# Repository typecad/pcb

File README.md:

# [typeCAD/pcb](https://github.com/typeCAD/pcb)

🤖 programmatically 💥 create 🛰️ hardware

**typeCAD** is a way to programmatically create hardware designs — KiCAD + TypeScript + npm. `@typecad/pcb` is the core package: schematics, PCB layout, placement, autorouting, zones, stitching, simulation, and a built-in gerber board viewer, with passives built in.

It's done with TypeScript and all the awesomeness of the npm/Node.js ecosystem.

- npm packages can be imported into your projects
- create portable/importable/shareable packages
- semantic version control

The schematic portion of hardware design is replaced with a few simple TypeScript classes. Rather than clicking and dragging, a line of code creates a component, and another line connects it. Sections of code can be turned into reusable modules and those modules can be turned into npm packages.

Code can be version controlled, status tracked, git push/pull/PR/issues can be used, and all the typical tools for software design can be used for hardware design now

## Example
_This **type**CAD code..._
```ts
import { Component, PCB, Resistor, LED } from '@typecad/pcb'

let typecad = new PCB('typecad');
let bt1 = new Component({ footprint: 'Battery:BatteryHolder_Keystone_500' });
let r1 = new Resistor({ value: '1 kOhm', size: '0805' });
let d1 = new LED();

typecad.named('vin').net(bt1.pin(1), r1.pin(1));
typecad.net(r1.pin(2), d1.pin(2));
typecad.named('gnd').net(d1.pin(1), bt1.pin(2));

typecad.create(r1, d1, bt1);
```

_...is the same as this schematic._

>The difference is that code can be copied, turned into reusable packages, version controlled, and used within the npm/Node.js system.

## Passives

Resistors, capacitors, inductors, diodes, LEDs, and fuses are built in — no second package. The SMD package size is a constructor option (default `0603`), and an explicit `footprint` always wins:

```ts
import { PCB, Resistor, Capacitor, Connector, TestPoint, MountingHole, NetTie } from '@typecad/pcb'

let r1 = new Resistor({ value: '4.7 kOhm' });                 // 0603 (default)
let r2 = new Resistor({ value: '10 kOhm', size: '0805' });    // explicit size
let c1 = new Capacitor({ value: '100 nF', voltage: '6.3 V' });
let j1 = new Connector({ number: 4, series: 'JST-SH' });      // footprint templated from the pin count
```

Sizes: `'0201' | '0402' | '0603' | '0805' | '1206' | '1210'` (fuses from `'0603'` up). Inside a `Package`, `this.passives.Capacitor(...)` works out of the box; shift a whole package with `{ passiveSize: '0805' }`.

## Get started
Read through the [documentation](https://typecad.net/getting-started) for a full walkthrough:

```bash
npx @typecad/pcb create
```

## Board viewer

This package ships a built-in, zero-dependency Gerber (RS-274X) + Excellon viewer:

```bash
# one-shot: render a fab-output directory to a self-contained interactive HTML file
npx gerber-viewer gerbers/ -o board-view.html --open
```

A ruler button in the toolbar arms a measurement mode: click a start point, move the mouse to
see the live distance, click again to stick the ruler — measurements accumulate, and `Esc`
clears them all. Hold `Shift` while measuring to snap the endpoint to 0/45/90-degree angles.
Rulers scale and pan with the board, keep a constant on-screen size while
zooming, and follow the dark/light theme.

The viewer also understands what it is showing: KiCad's X2 object attributes (`%TO.N` net,
`%TO.P` component/pin) are parsed, so hovering copper shows the net and pad in the readout,
and clicking highlights the whole net (pad→net comes from the project netlist, passed with
`--netlist`). A search box locates components — type `U3`, press Enter, and the view zooms to
its pads. A collapsible *fab report* panel lists board dimensions, per-layer trace lengths and
min/max widths, and the drill table. DRC violations from the build's `_drc.json` are drawn as
red markers when passed with `--drc` (hover for the message, toggle with the `DRC` button).
The `SVG`/`PNG` buttons export the current view — theme, layer visibility and highlight
included — as a vector file or a ~1600-pixel raster image.

Programmatic use (parsing, layer detection, SVG rendering):

```ts
import {
  parseGerber, parseExcellon, detectLayer, renderSvg,
  buildViewerFromFiles,
} from '@typecad/pcb/gerber-viewer';
```

### PCBA image render

The same gerbers can be rendered as a flat, themed 2D "assembled board" image — the
PcbDraw look, computed from gerbers alone (no board file, no KiCad install, no
lighting or perspective). The substrate is the stitched Edge.Cuts outline, the
soldermask film is composited over copper with its openings punched through an SVG
mask so pads show in the finish color, copper traces and pours ghost through the
film in a darker mask tone (`maskCopper` theme color — real mask is translucent),
and components are stylized Fritzing-style glyphs (body, metal leads, pin-1 dot,
DIP notch) inferred from the X2 `%TO.P` pad attributes — no part library needed:

```bash
npx gerber-viewer gerbers/ --render pcba -o board-pcba.svg
npx gerber-viewer gerbers/ --render pcba --style blueprint -o board-drawing.svg
```

A sibling netlist is picked up automatically when it sits next to the gerber
directory (the typeCAD build layout: `build/gerbers` + `build/<board>.net`) — pass
`--netlist` to point at one explicitly, or `--no-netlist` to render from pad
topology alone.

With a KiCad netlist (`--netlist`, the same flag the viewer uses), each ref's
footprint name and value select the glyph: names map to a package grammar —
chips (`R_0603_1608Metric` renders the real 1.6 × 0.8 mm body), SOIC/TSSOP,
DIPs with a notch, QFN/DFN and BGA, QFP, SOT/TO transistors with tabs, pin
headers, terminal blocks with screw dots, shrouded connectors (USB, barrel
jacks, JST), crystals, metal-can modules (oscillators, RF shields), trimmer
pots, slide switches, rotary encoders, radial electrolytic cans, TH LED domes,
pushbuttons — and pad topology classifies anything the name table doesn't
know, with reference prefixes picking up the slack (an `RV` on three TH pads
is a trimmer, an `LED` on two is a dome). When the fab gerber
(`F_Fab`/`B_Fab`) is in the set, the exact body dimensions come from there: the
largest closed fab contour per component supplies the body rectangle (orientation
cuts like QFN pin-1 chamfers are squared off — the pin-1 dot marks orientation),
so land-pattern pads peek past the package exactly as on the real part. The
reference prefix and value then choose the appearance: through-hole resistors
get the classic tan body with real color bands ("10k" → brown black orange +
gold), MLCCs render beige, inductors charcoal with winding stripes, diodes
carry a cathode stripe, LEDs a translucent tint. Without a netlist everything
still renders from pad geometry alone, just without exact body dims and
decorations.

Themes are a small PcbDraw-style palette (`green-enig` — the classic green
default, plus `typecad` — the house look: deep teal mask, champagne-gold
pads — `purple-enig`, `black-hasl`, `blue-enig`) or your own JSON (`--theme my-theme.json` overrides any subset of the
colors, including `maskCopper`). Refdes labels default to auto: off when the
silkscreen layer already carries them (a synthetic label would double the silk
text — and the board's own text renders faithfully since KiCad vectorizes fonts
like `OCR A Std` into the gerber), on when there is none — `--labels`/`--no-labels`
forces either way. Synthetic labels use the theme's `labelFont`
(`'OCR A Std', 'Courier New', monospace` by default) to match typeCAD boards.
Every render carries an engineering title block below the board — name, date,
dimensions, and a "made with typeCAD" wordmark; `--no-title-block` renders a
clean image. `--style blueprint` draws the board as an engineering drawing
instead of an assembled render: blueprint paper, board
and component outlines in ink, outlined pads, drill marks, and the title block in
drawing ink; designators come from the fab layer (synthetic labels only without one).

A combo box under the board title switches between **Gerber view** (the classic per-layer stack with
visibility/opacity controls), **PCBA view** (the flat assembled render described above), and **Blueprint
view** (the engineering drawing). All views share one
coordinate frame, so pan/zoom, the measurement ruler, DRC markers, component search and the vscode cross-probing
(double-click a component to jump to its source line; select one in the editor to highlight it here) all work in either
view. The PCBA view hides the layer controls — there is only one layer stack to show — and the choice is remembered
per board.

Inside VS Code, the bundled typeCAD/pcb extension renders this viewer (gerbers + netlist + DRC) in a Board panel that refreshes on every `npm run build` and cross-probes both ways with the source — see the package docs. Layer visibility and opacity settings persist across rebuilds — they're stored in your browser (localStorage, keyed per board) and re-applied when the page reloads. A dark/light theme toggle sits in the sidebar header; the theme (including the board canvas) is saved per browser and follows your OS preference on first visit. On the dark canvas, near-black layer colors (silkscreen, paste, drill) are automatically recolored so they stay visible, and clear-polarity cutouts follow the canvas color.

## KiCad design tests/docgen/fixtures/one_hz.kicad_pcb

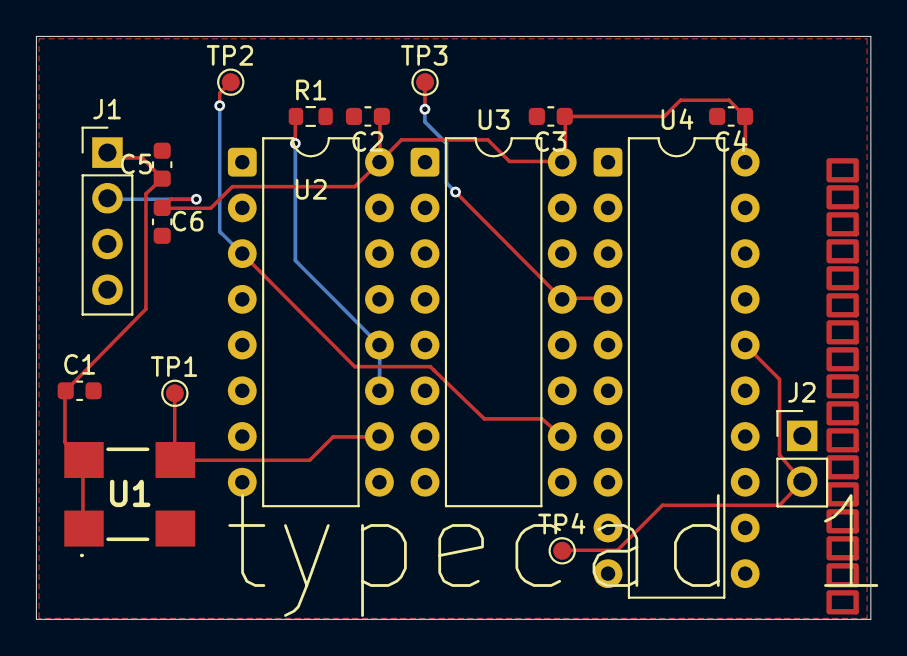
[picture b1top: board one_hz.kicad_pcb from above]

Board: 2 copper layers, 46.4 x 32.4 mm, 17 parts (0 on the bottom side), 8 nets.

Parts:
C1, C2, C3, C4: 100nF; C_0603_1608Metric
C5, C6: 10µF; C_0603_1608Metric
J1: PinHeader_1x04_P2.54mm_Vertical
J2: PinHeader_1x02_P2.54mm_Vertical
R1: 10kΩ; R_0603_1608Metric
TP1, TP2, TP3, TP4: TestPoint_Pad_D1.0mm
U1: SIT8008BI-82-30E-4.194304; QFN_7050_4pins
U2: 74HC4060N; DIP-16_W7.62mm
U3: 74HC4040N; DIP-16_W7.62mm
U4: 74HC244N; DIP-20_W7.62mm

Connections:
1HZ_BUFFERED: J2.2, TP4.1, U4.16
1HZ_UNBUFFERED: TP3.1, U3.13, U4.4
256HZ: TP2.1, U2.3, U3.10
+3V: C1.1, C5.1, J1.1, U1.1, U1.4
+5V: C2.1, C3.1, C4.1, C6.1, J1.2, U2.16, U3.16, U4.20
GND: C1.2, C2.2, C3.2, C4.2, C5.2, C6.2, J1.3, J1.4, J2.1, R1.2, U1.2, U2.1, U2.2, U2.4, U2.5, U2.6, U2.7, U2.8, U2.13, U2.14, U2.15, U3.1, U3.2, U3.3, U3.4, U3.5, U3.6, U3.7, U3.8, U3.9, U3.11, U3.12, U3.14, U3.15, U4.1, U4.2, U4.5, U4.10, U4.15, U4.17, U4.18, U4.19
OSC_OUT: TP1.1, U1.3, U2.10
RESET: R1.1, U2.11, U2.12

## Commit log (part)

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2026-05-11 kicad2typcad mvp
2026-05-12 kicad2typecad
2026-05-13 all tests passing
2026-05-20 any removal
2026-05-21 huge router improvements
2026-05-21 dep consolidation
2026-05-22 many refactor improvements
2026-05-23 feat: Add PCB board serializer and existing board parser
    - Implemented `pcb_board_serializer.ts` for rendering vias, outlines, tracks, graphics, zones, and keepout zones in the PCB context.
    - Introduced `pcb_existing_board.ts` to parse existing board elements and manage net mappings.
    - Created `pcb_net_merger.ts` to handle merging of schematic and existing board nets, ensuring unique net codes.
    - Added a critique document for the typeCAD package, highlighting critical issues, architecture problems, code quality issues, and test gaps.
2026-05-23 added typecad cli
2026-05-23 docgen improvements
2026-05-23 minor docgen improvements
2026-05-24 major docgen rewrite
2026-05-24 gitdiff refactor and feature add
2026-05-24 gitdiff improvements
2026-05-24 git diff net and bom diff
2026-05-25 gitdiff refactor and improvements
2026-05-25 gitdiff merged into typecad
2026-05-25 docgen and gitdiff merged
2026-05-26 typecad normalization of build config
2026-05-26 typecad bin features
2026-05-30 major refactoring
2026-05-31 linux flatpak updates
2026-05-31 flatpak
2026-06-01 kicad2typecad refactor
2026-06-01 removed obfuscation and changed license
2026-06-01 production changes
2026-06-01 more prod fixes
2026-06-02 0.3.2
2026-06-03 tests and minor doctor fixes
2026-06-04 0.3.4
2026-06-05 changed to syn and contract refactor
